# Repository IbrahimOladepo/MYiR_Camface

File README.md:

# MYiR_Camface
This is a PCB to interface regular 22-pin MIPI cameras to the 24-pin MYiR dev boards. 

## PCB Render

## Impedance Calculation

Differential impedance for the MIPI CSI pairs, calculated with the JLCPCB impedance calculator.

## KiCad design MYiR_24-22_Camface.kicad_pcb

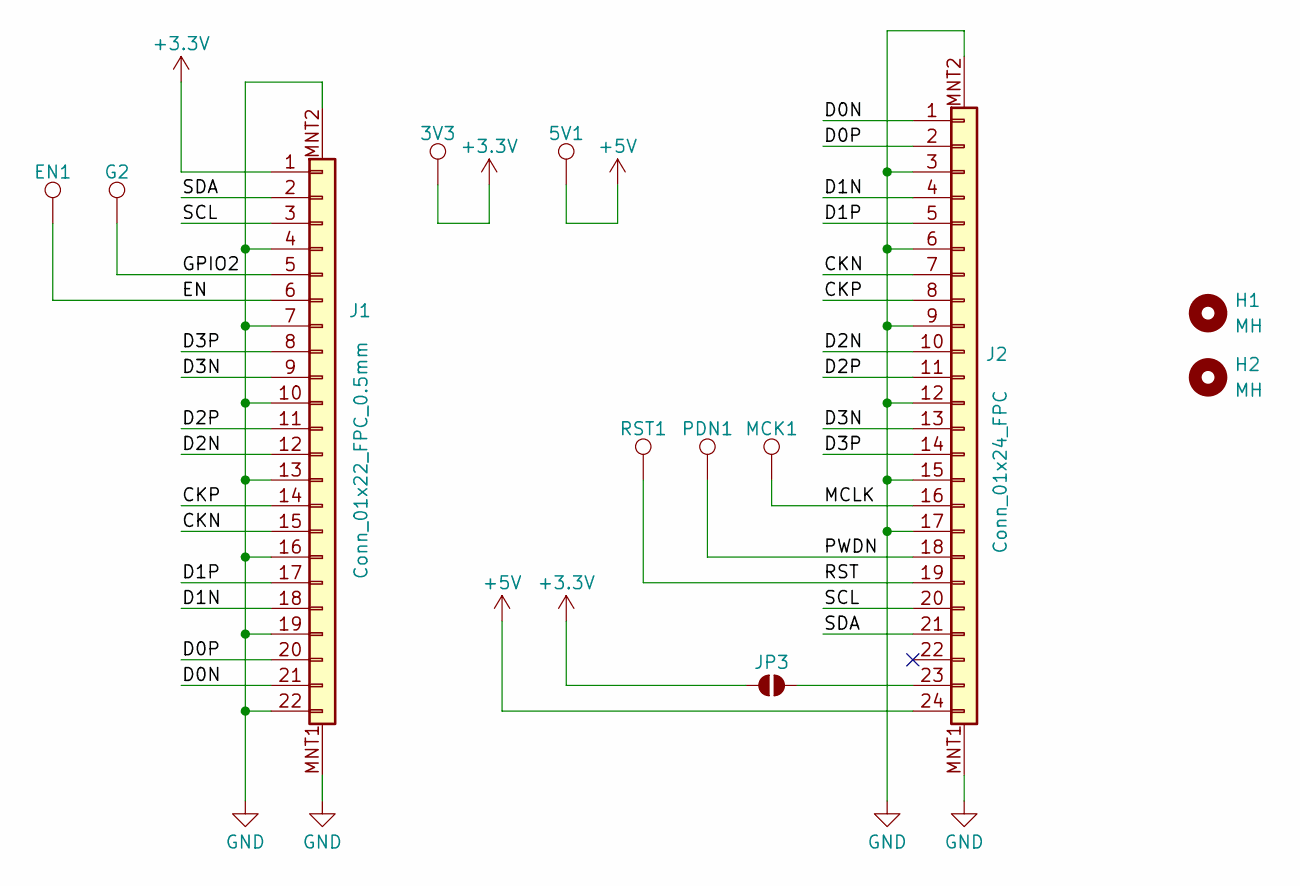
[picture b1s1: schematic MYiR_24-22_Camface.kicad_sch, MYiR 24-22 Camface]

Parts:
3V3, 5V1: PTH; Pin_D1.0mm_L10.0mm
EN1: PTH; Pin_D0.7mm_L6.5mm_W1.8mm_FlatFork
G2: PTH; Pin_D0.7mm_L6.5mm_W1.8mm_FlatFork
H1, H2: MH; MountingHole_2.7mm_M2.5_DIN965
J1: Conn_01x22_FPC_0.5mm; FPC_1x22_P0.5mm_Horizontal_BottomContact; Manufacturer Part # FPC0.5B-WTG-22P; LCSC Part # C22360344
J2: Conn_01x24_FPC; FPC_1x24_P0.5mm_Horizontal_BottomContact; Manufacturer Part # FPC-0.5FX-24PWBH20; LCSC Part # C3446015
JP3: Jumper_2_NO
MCK1: PTH; Pin_D0.7mm_L6.5mm_W1.8mm_FlatFork
PDN1: PTH; Pin_D0.7mm_L6.5mm_W1.8mm_FlatFork
RST1: PTH; Pin_D0.7mm_L6.5mm_W1.8mm_FlatFork

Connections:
+3.3V: 3V3.1 (1_1), J1.1, JP3.1 (A)
+5V: 5V1.1 (1_1), J2.24
/CKN: J1.15, J2.7
/CKP: J1.14, J2.8
/D0N: J1.21, J2.1
/D0P: J1.20, J2.2
/D1N: J1.18, J2.4
/D1P: J1.17, J2.5
/D2N: J1.12, J2.10
/D2P: J1.11, J2.11
/D3N: J1.9, J2.13
/D3P: J1.8, J2.14
/EN: EN1.1 (1_1), J1.6
/GPIO2: G2.1 (1_1), J1.5
/MCLK: J2.16, MCK1.1 (1_1)
/PWDN: J2.18, PDN1.1 (1_1)
/RST: J2.19, RST1.1 (1_1)
/SCL: J1.3, J2.20
/SDA: J1.2, J2.21
GND: J1.4, J1.7, J1.10, J1.13, J1.16, J1.19, J1.22, J1.MNT1, J1.MNT2, J2.3, J2.6, J2.9, J2.12, J2.15, J2.17, J2.MNT1, J2.MNT2
unnamed: J2.23, JP3.2 (B)

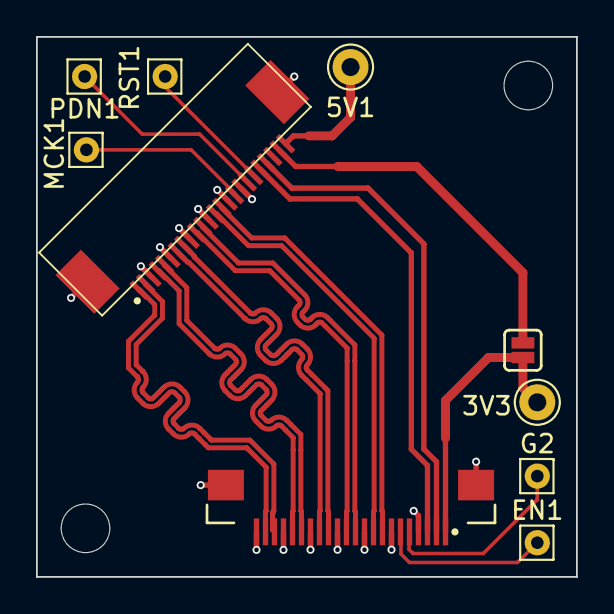
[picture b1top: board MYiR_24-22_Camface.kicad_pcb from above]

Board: 2 copper layers, 30.0 x 30.0 mm, 12 parts (0 on the bottom side), 21 nets.

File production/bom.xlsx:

Designator | Footprint | Quantity | Value | LCSC Part #
J1 | FPC_1x22_P0.5mm_Horizontal_BottomContact | 1 | Conn_01x22_FPC_0.5mm | C22360344
J2 | FPC_1x24_P0.5mm_Horizontal_BottomContact | 1 | Conn_01x24_FPC | C3446015
